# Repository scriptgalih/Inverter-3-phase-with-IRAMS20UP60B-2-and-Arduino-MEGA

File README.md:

Inverter 3 phase with IRAMS20UP60B-2 and Arduino MEGA

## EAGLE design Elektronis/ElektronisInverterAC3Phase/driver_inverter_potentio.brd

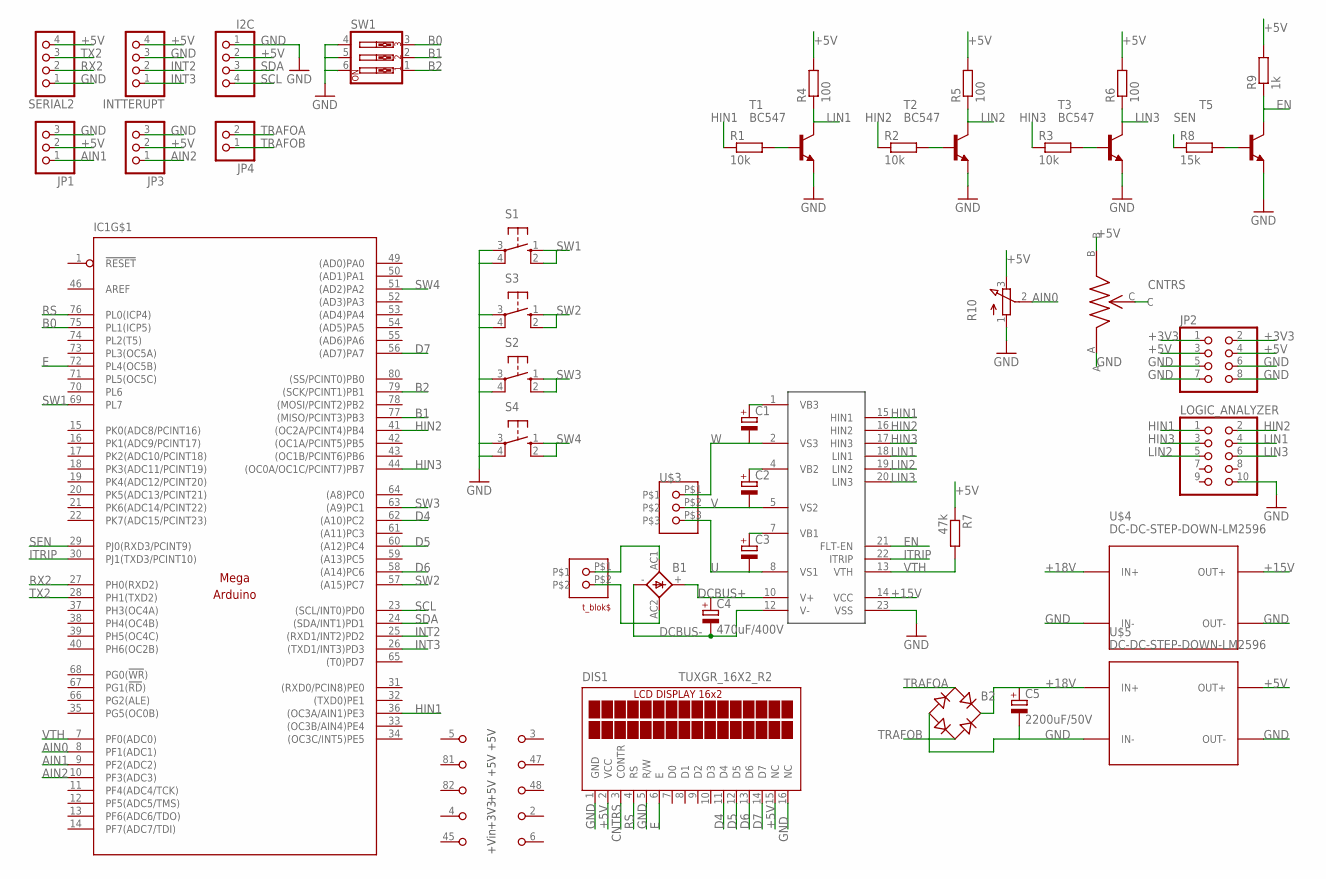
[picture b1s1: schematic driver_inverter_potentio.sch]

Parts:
B1: GBPC80X
B2: RB1A
C1, C2, C3: CPOL-EUE2.5-6; E2,5-6
C4: 470uF/400V; EB25D
C5: 2200uF/50V; E7,5-16
DIS1: TUXGR_16X2_R2
I2C: PINHD-1X4; 1X04
IC1: MEGAARDUINO_22; MEGA_ARDUINO_2
INTTERUPT: PINHD-1X4; 1X04
JP1, JP3: PINHD-1X3; 1X03
JP2: PINHD-2X4; 2X04
JP4: PINHD-1X2; 1X02
LOGIC_ANALYZER: PINHD-2X5; 2X05
R1, R2, R3: 10k; 0207/10
R4, R5, R6: 100; 0207/10
R7: 47k; 0207/10
R8: 15k; 0207/10
R9: 1k; 0207/10
R10: 3RP/1610N
S1, S2, S3, S4: 10-XX; B3F-10XX
SERIAL2: PINHD-1X4; 1X04
SW1: SW_DIP-3; EDG-03
T1, T2, T3: BC547; TO92
T5: BC317-NPN-TO92-EBC; TO92-EBC
U$1: IRAMS
U$2: TBLOCK_1X2
U$3: TBLOCK_3PIN; TBLOCK_1X3
U$4, U$5: DC-DC-STEP-DOWN-LM2596
U$6: POTENSIO

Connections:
+3V3: IC1.2 (+3V3), JP2.1, JP2.2
+5V: DIS1.2 (VCC), DIS1.15 (NC), I2C.2, IC1.3 (+5V), IC1.47 (+5V), IC1.48 (+5V), INTTERUPT.4, JP1.2, JP2.3, JP2.4, JP3.2, R4.2, R5.2, R6.2, R7.1, R9.2, R10.3 (E), SERIAL2.4, U$5.OUT+, U$6.B
+15V: U$1.14 (VCC), U$4.OUT+
+18V: B2.+, C5.+, U$4.IN+, U$5.IN+
+VIN: IC1.6 (+VIN)
AIN0: IC1.8 (PF1(ADC1)), R10.2 (S)
AIN1: IC1.9 (PF2(ADC2)), JP1.1
AIN2: IC1.10 (PF3(ADC3)), JP3.1
B0: IC1.75 (PL1(ICP5)), SW1.3
B1: IC1.77 ((MISO/PCINT3)PB3), SW1.2
B2: IC1.79 ((SCK/PCINT1)PB1), SW1.1
CNTRS: DIS1.3 (CONTR), U$6.C
D4: DIS1.11 (D4), IC1.62 ((A10)PC2)
D5: DIS1.12 (D5), IC1.60 ((A12)PC4)
D6: DIS1.13 (D6), IC1.58 ((A14)PC6)
D7: DIS1.14 (D7), IC1.56 ((AD7)PA7)
DCBUS+: B1.+, C4.+, U$1.10 (V+)
DCBUS-: B1.-, C4.-, U$1.12 (V-)
E: DIS1.6 (E), IC1.72 (PL4(OC5B))
EN: R9.1, T5.C, U$1.21 (FLT-EN)
GND: B2.-, C5.-, DIS1.1 (GND), DIS1.5 (R/W), DIS1.16 (NC), I2C.1, IC1.4 (GND), IC1.5 (GND), IC1.45 (GND), IC1.81 (GND), IC1.82 (GND), INTTERUPT.3, JP1.3, JP2.5, JP2.6, JP2.7, JP2.8, JP3.3, LOGIC_ANALYZER.10, R10.1 (A), S1.3, S1.4 (P1), S2.3, S2.4 (P1), S3.3, S3.4 (P1), S4.3, S4.4 (P1), SERIAL2.1, SW1.4, SW1.5, SW1.6, T1.1 (E), T2.1 (E), T3.1 (E), T5.E, U$1.23 (VSS), U$4.IN-, U$4.OUT-, U$5.IN-, U$5.OUT-, U$6.A
HIN1: IC1.36 ((OC3A/AIN1)PE3), LOGIC_ANALYZER.1, R1.1, U$1.15 (HIN1)
HIN2: IC1.41 ((OC2A/PCINT4)PB4), LOGIC_ANALYZER.2, R2.1, U$1.16 (HIN2)
HIN3: IC1.44 ((OC0A/OC1C/PCINT7)PB7), LOGIC_ANALYZER.3, R3.1, U$1.17 (HIN3)
INT2: IC1.25 ((RXD1/INT2)PD2), INTTERUPT.2
INT3: IC1.26 ((TXD1/INT3)PD3), INTTERUPT.1
ITRIP: IC1.30 (PJ1(TXD3/PCINT10)), U$1.22 (ITRIP)
LIN1: LOGIC_ANALYZER.4, R4.1, T1.3 (C), U$1.18 (LIN1)
LIN2: LOGIC_ANALYZER.5, R5.1, T2.3 (C), U$1.19 (LIN2)
LIN3: LOGIC_ANALYZER.6, R6.1, T3.3 (C), U$1.20 (LIN3)
unnamed: C1.+, U$1.1 (VB3)
unnamed: R1.2, T1.2 (B)
unnamed: C2.+, U$1.4 (VB2)
unnamed: R3.2, T3.2 (B)
unnamed: R2.2, T2.2 (B)
unnamed: C3.+, U$1.7 (VB1)
unnamed: B1.AC1, U$2.P$1
unnamed: B1.AC2, U$2.P$2
unnamed: R8.2, T5.B
RS: DIS1.4 (RS), IC1.76 (PL0(ICP4))
RX2: IC1.27 (PH0(RXD2)), SERIAL2.2
SCL: I2C.4, IC1.23 ((SCL/INT0)PD0)
SDA: I2C.3, IC1.24 ((SDA/INT1)PD1)
SEN: IC1.29 (PJ0(RXD3/PCINT9)), R8.1
SW1: IC1.69 (PL7), S1.1 (S), S1.2 (S1)
SW2: IC1.57 ((A15)PC7), S3.1 (S), S3.2 (S1)
SW3: IC1.63 ((A9)PC1), S2.1 (S), S2.2 (S1)
SW4: IC1.51 ((AD2)PA2), S4.1 (S), S4.2 (S1)
TRAFOA: B2.AC1, JP4.2
TRAFOB: B2.AC2, JP4.1
TX2: IC1.28 (PH1(TXD2)), SERIAL2.3
U: C3.-, U$1.8 (VS1), U$3.P$3
V: C2.-, U$1.5 (VS2), U$3.P$2
VTH: IC1.7 (PF0(ADC0)), R7.2, U$1.13 (VTH)
W: C1.-, U$1.2 (VS3), U$3.P$1

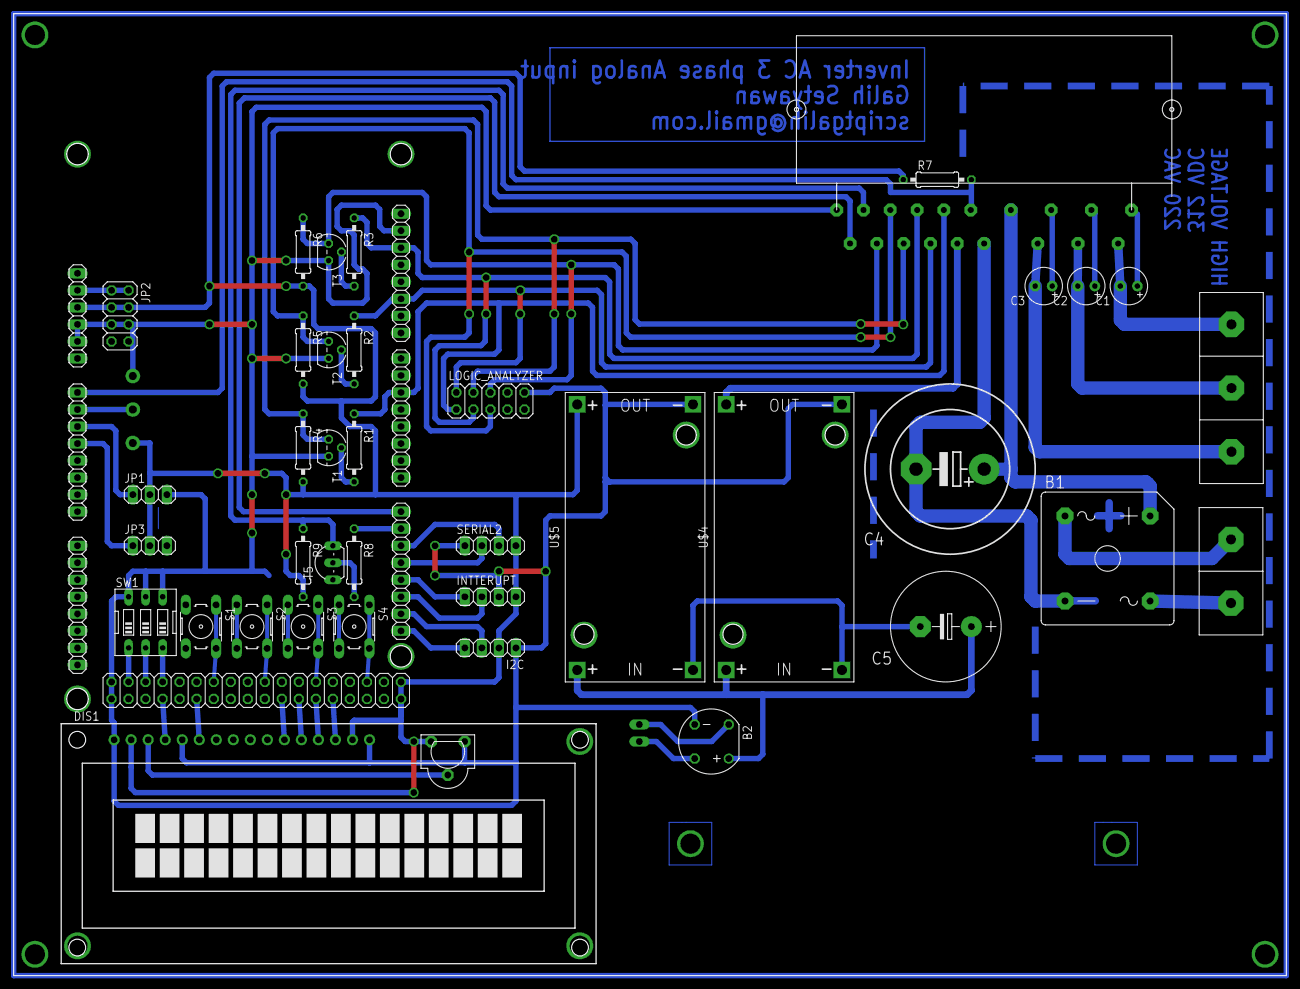
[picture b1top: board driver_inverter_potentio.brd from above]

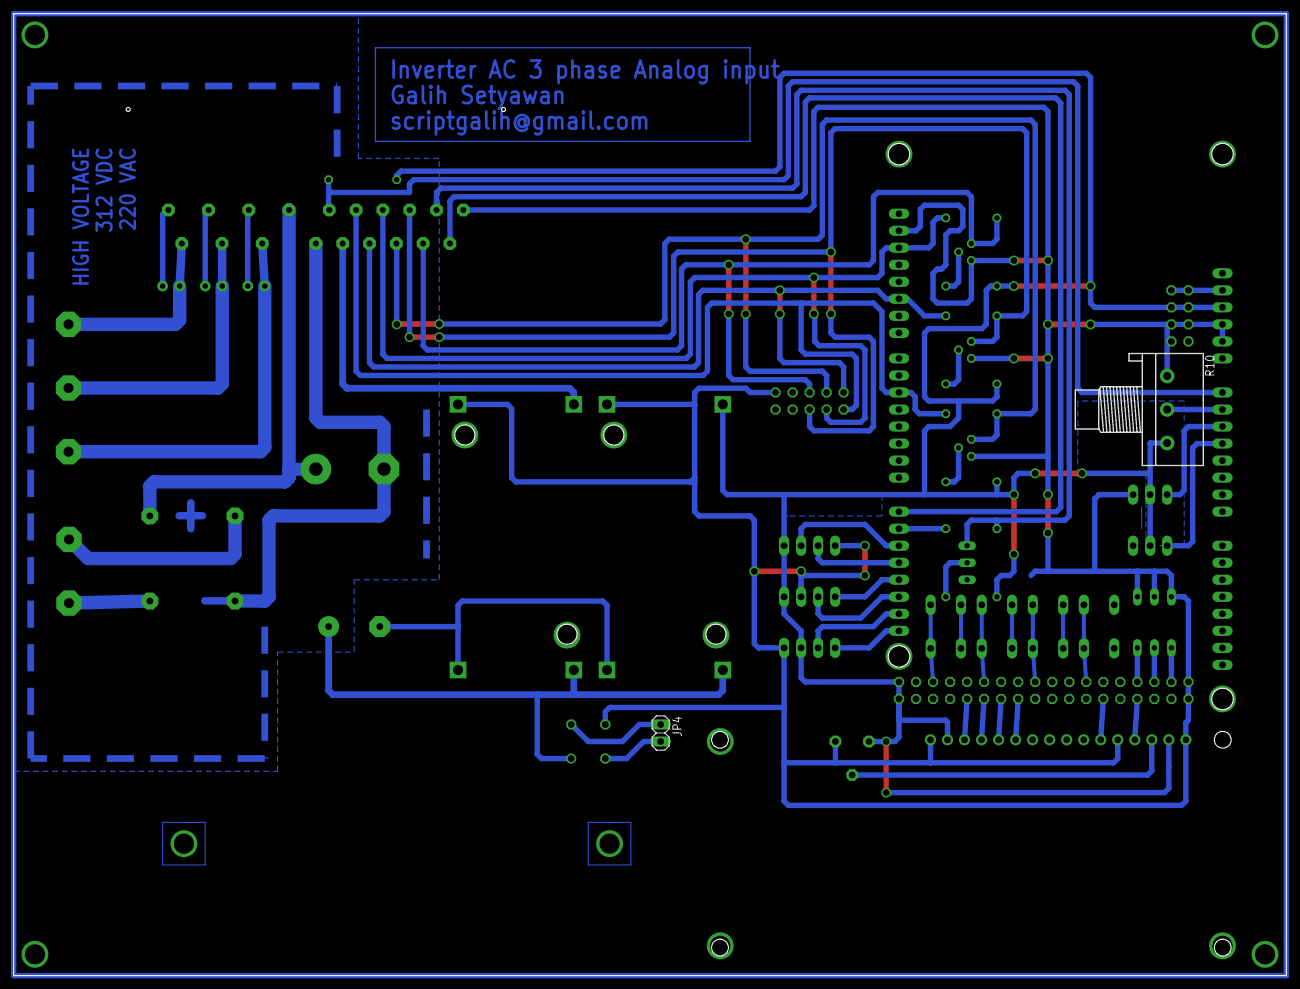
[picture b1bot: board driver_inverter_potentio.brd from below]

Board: 2 copper layers, 189.9 x 143.5 mm, 42 parts (2 on the bottom side), 54 nets.

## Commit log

2019-09-28 fix shocket analizer
    [eagle] menambahkan dioda jembatan pada input trafo

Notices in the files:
parts and their libraries:
diy-modules: Released under the Creative Commons Attribution 4.0 International License: http://creativecommons.org/licenses/by/4.0
